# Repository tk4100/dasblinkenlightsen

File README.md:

# dasblinkenlightsen
CAD and source for an aerial wingtip flasher.

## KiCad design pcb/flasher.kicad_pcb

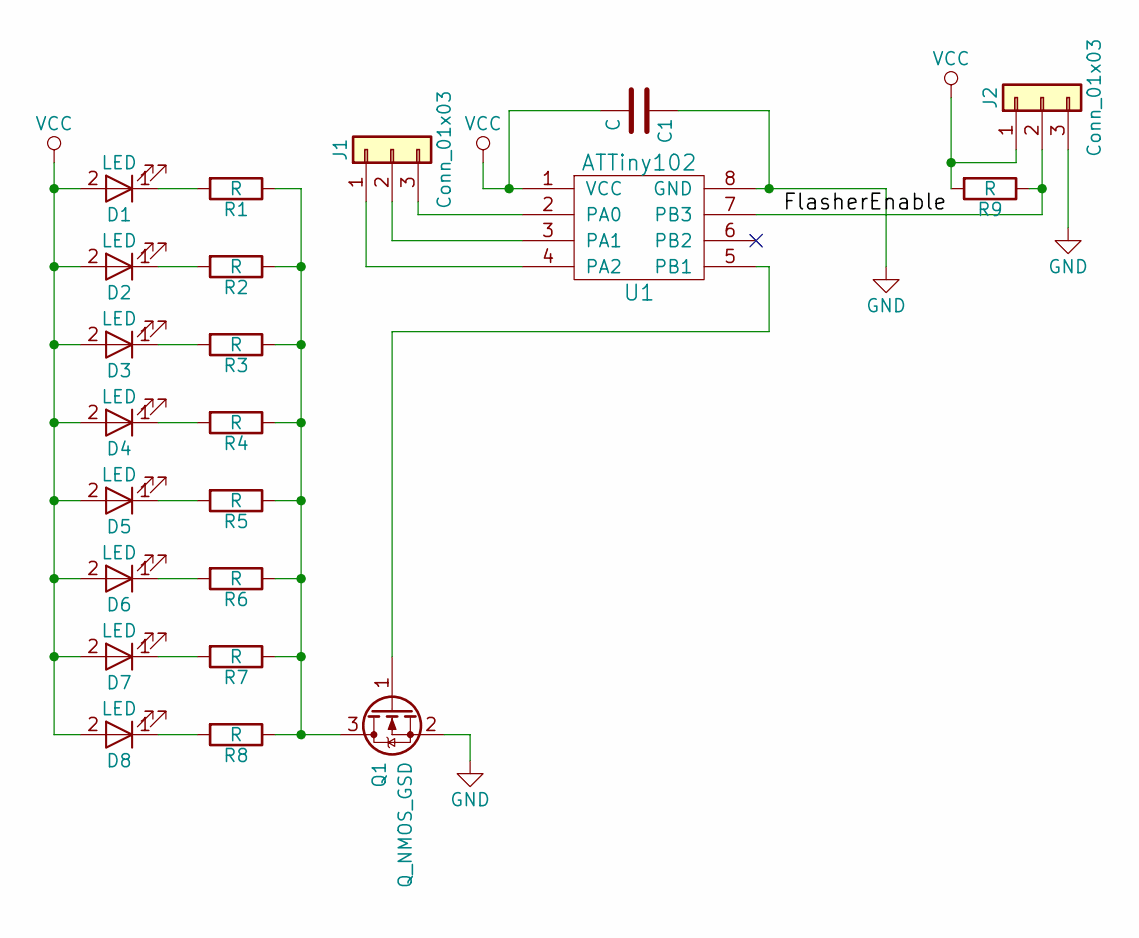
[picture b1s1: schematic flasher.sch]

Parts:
C1: C; C_0805
D1, D2, D3, D4, D5, D6, D7, D8: LED; LED_0603
J1: Conn_01x03; Pin_Header_Straight_1x03_Pitch1.27mm
J2: Conn_01x03; Pin_Header_Straight_1x03_Pitch2.54mm
Q1: Q_NMOS_GSD; SOT-23
R1, R2, R3, R4, R5, R6, R7, R8, R9: R; R_0805
U1: ATTiny102; SOIC-8_3.9x4.9mm_Pitch1.27mm

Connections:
/FlasherEnable: J2.2, R9.1, U1.7 (PB3)
GND: C1.1, J2.3, Q1.2 (S), U1.8 (GND)
unnamed: D1.1 (K), R1.2
unnamed: D2.1 (K), R2.2
unnamed: D3.1 (K), R3.2
unnamed: D4.1 (K), R4.2
unnamed: D5.1 (K), R5.2
unnamed: D6.1 (K), R6.2
unnamed: D7.1 (K), R7.2
unnamed: D8.1 (K), R8.2
unnamed: J1.1, U1.4 (PA2)
unnamed: J1.2, U1.3 (PA1)
unnamed: J1.3, U1.2 (PA0)
unnamed: Q1.1 (G), U1.5 (PB1)
unnamed: Q1.3 (D), R1.1, R2.1, R3.1, R4.1, R5.1, R6.1, R7.1, R8.1
VCC: C1.2, D1.2 (A), D2.2 (A), D3.2 (A), D4.2 (A), D5.2 (A), D6.2 (A), D7.2 (A), D8.2 (A), J2.1, R9.2, U1.1 (VCC)

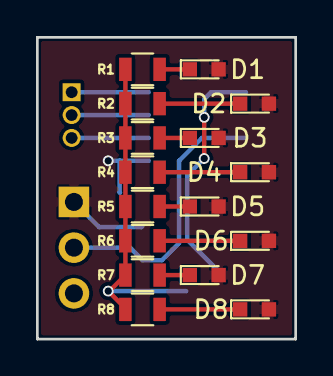
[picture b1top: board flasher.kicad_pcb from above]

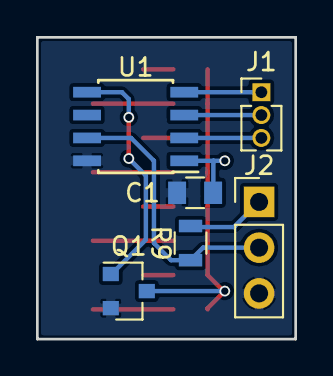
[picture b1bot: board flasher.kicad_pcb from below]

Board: 2 copper layers, 14.4 x 16.8 mm, 22 parts (6 on the bottom side), 16 nets.

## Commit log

2018-01-08 import pcb files
2018-01-09 add flasher code
